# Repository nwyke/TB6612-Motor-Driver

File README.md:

# TB6612-Motor-Driver
Stepper / DC Motor Driver based on TB6612 available at MiniElektro.dk/.se

Here you have the opportunity to drive 2 DC motors or one stepper, from this TB6612 breakout board.
The board is compatible with motors up to 1.2A.

Please support us and open-source hardware by purchasing products from
[MiniElektro.dk](http://minielektro.dk)/[MiniElektro.se](http://minielektro.se).

Content
-------------------
* **/Hardware**
  * All Eagle design files (.brd, .sch)

License
-------------------
The hardware is released under [Creative Commons ShareAlike 4.0 International](https://creativecommons.org/licenses/by-sa/4.0/).

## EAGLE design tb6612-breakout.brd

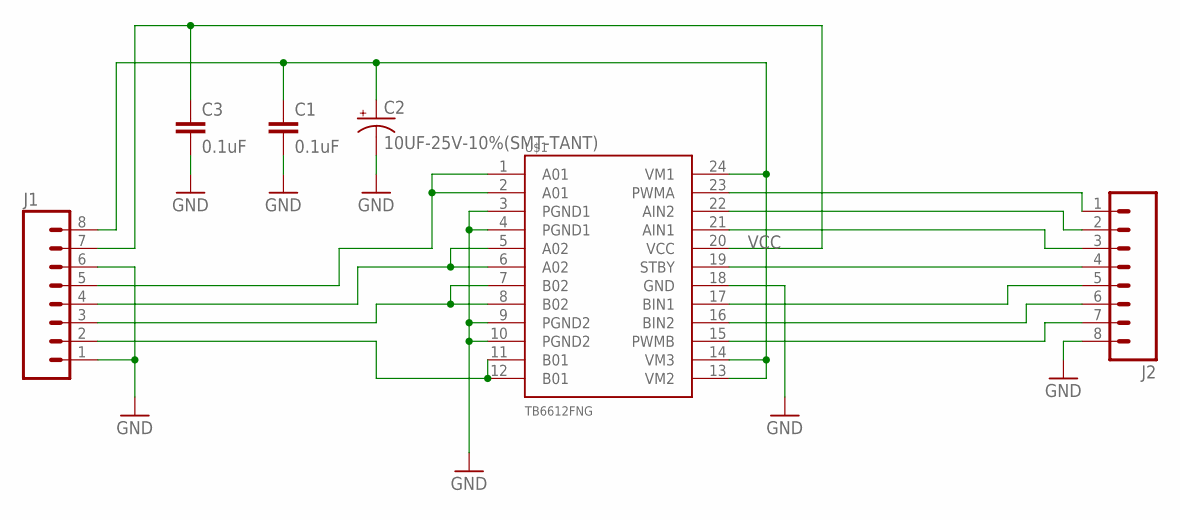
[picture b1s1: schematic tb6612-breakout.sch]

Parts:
C1, C3: 0.1uF; 0603-CAP
C2: 10UF-25V-10%(SMT-TANT); EIA6032-NOM
J1, J2: M08SILK_FEMALE_PTH; 1X08
U$1: TB6612FNG; SSOP24

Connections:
GND: C1.2, C2.C (-), C3.2, J1.1, J1.6, J2.8, U$1.3 (PGND1), U$1.4 (PGND1), U$1.9 (PGND2), U$1.10 (PGND2), U$1.18 (GND)
unnamed: J2.1, U$1.23 (PWMA)
unnamed: J2.2, U$1.22 (AIN2)
unnamed: J2.3, U$1.21 (AIN1)
unnamed: J2.4, U$1.19 (STBY)
unnamed: J2.5, U$1.17 (BIN1)
unnamed: J2.6, U$1.16 (BIN2)
unnamed: J2.7, U$1.15 (PWMB)
unnamed: J1.2, U$1.11 (B01), U$1.12 (B01)
unnamed: J1.3, U$1.7 (B02), U$1.8 (B02)
unnamed: J1.4, U$1.5 (A02), U$1.6 (A02)
unnamed: J1.5, U$1.1 (A01), U$1.2 (A01)
unnamed: C1.1, C2.A (+), J1.8, U$1.13 (VM2), U$1.14 (VM3), U$1.24 (VM1)
VCC: C3.1, J1.7, U$1.20 (VCC)

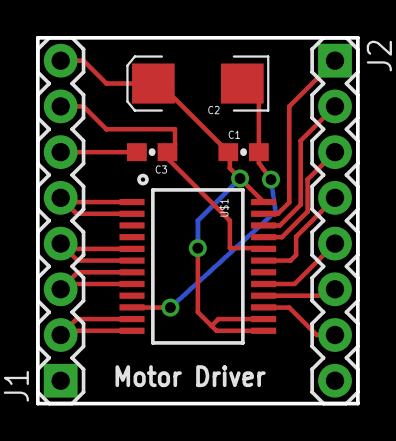
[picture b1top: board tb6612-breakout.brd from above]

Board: 2 copper layers, 17.8 x 20.3 mm, 6 parts (0 on the bottom side), 14 nets.

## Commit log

2016-04-23 Rev0 design #1616
2016-04-23 Create Hardware
2016-04-23 init
2016-04-23 Updated description
2016-05-20 Add content, license

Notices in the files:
parts and their libraries:
SparkFun-PowerIC: Licensing: Creative Commons ShareAlike 4.0 International - https://creativecommons.org/licenses/by-sa/4.0
